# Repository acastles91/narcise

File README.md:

# Installation instructions

1. Download [Visual Studio Code](https://code.visualstudio.com/) and once that is done, install [PlatformIO](https://docs.platformio.org/en/latest/integration/ide/vscode.html#installation).
2. Open a terminal window and install *numpy*, a python library, by running the following command in the terminal:
`pip3 install numpy`
3. Clone this repository in a folder that you can remember, by typing the following command into the terminal:
`git clone https://github.com/acastles91/narcise/`
	* Navigate through folders using the command `cd`
4. In **Visual Studio Code** go to *File > Open Folder* and open the folder *narciseFromScratch* inside the *narcise* directory that you just cloned. This is where you will compile the code that will go into the microcontroller.
5. Navigate to the *narcise* folder with the file browser. Inside of it you will find a directory called *scriptGenerator*. Open the file *script* with **TextEdit**.
6. Edit the script. Each line represents a keyframe, which you define by first defining the *Timestamp* with the format *hh:mm:ss:fff*, where fff represents fractions of a second in milliseconds. After that comes the value of opacity of each layer as a percentage, with 100 being transparent and 0 being totally opaque. It is important that you keep this format consistent throughout the whole file. Make sure that you leave **no extra whitespace at the end of the file*
7. After saving the script, go back to *Visual Studio Code*, with the folder *narciseFromScratch* opened. Go to the terminal and type:
`cd ../scriptGenerator`
`python3 scriptGenerator.py 1 200 7`

	The argument `1` means that the script will be looped, `200` is the refresh rate (the bigger the value the slower and more "flickery" the piece will look) and `7` is a parameter that relates to the difference between minimal and maximal value. Play around with this last parameter to see differences in the response time of the dimming.

8. After the script is generated, connect the microcontroller to the computer using a USB cable capable of transfering data and upload the program.

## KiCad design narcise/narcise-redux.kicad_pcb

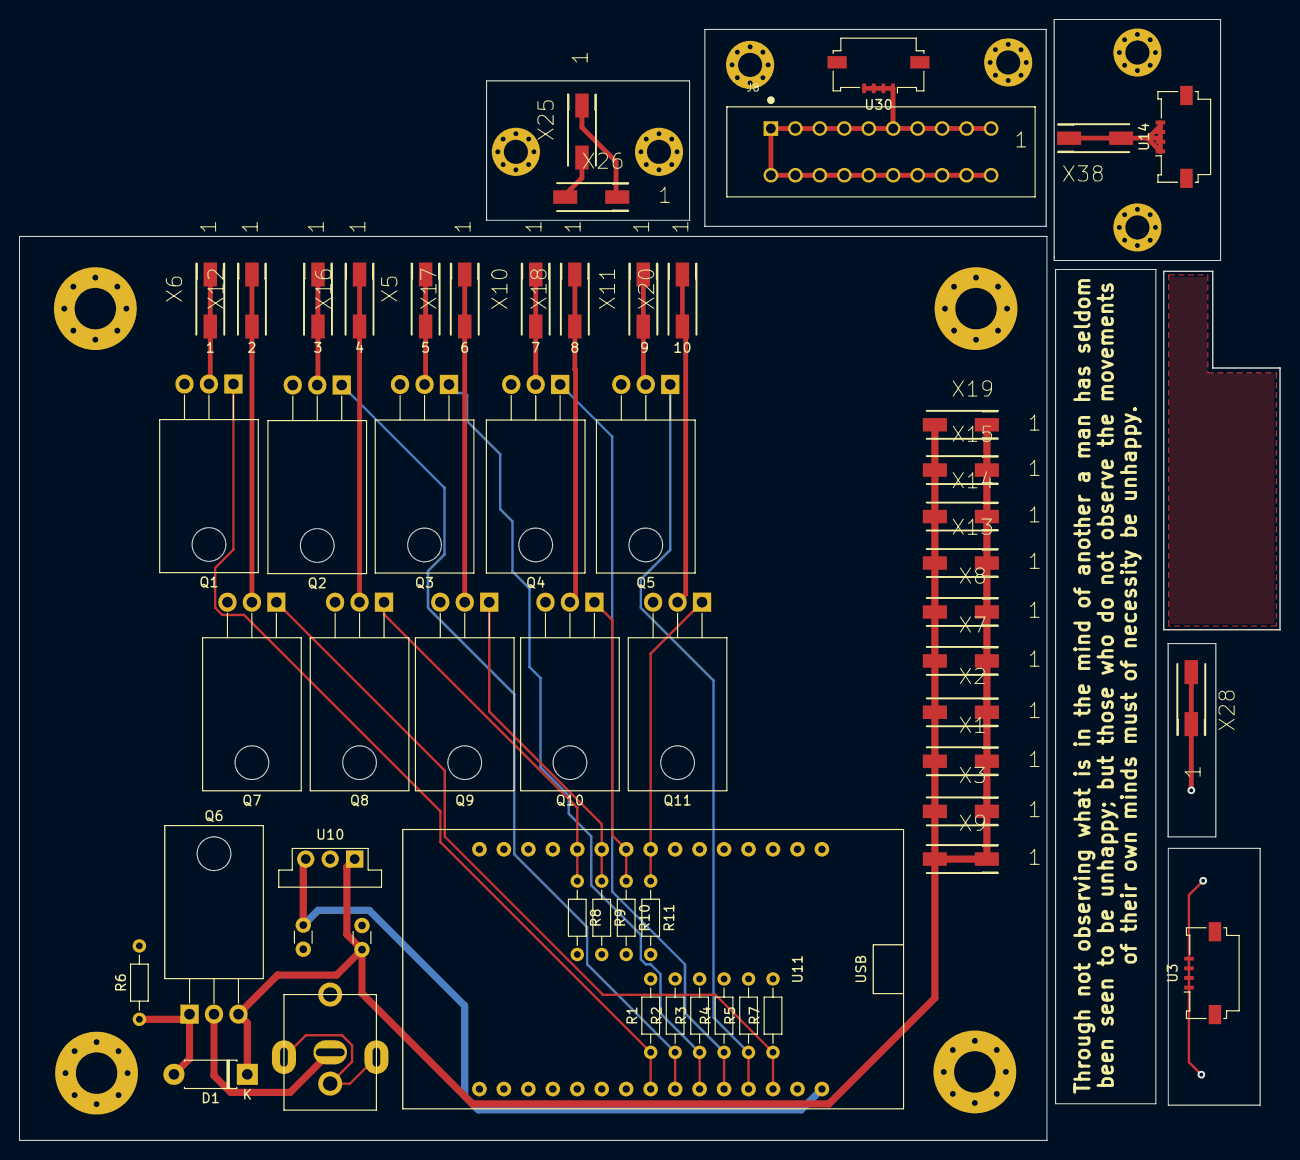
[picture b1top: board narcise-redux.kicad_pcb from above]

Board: 2 copper layers, 130.9 x 116.4 mm, 56 parts (0 on the bottom side), 31 nets.

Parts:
D1: D_Zener-10V; D_DO-41_SOD81_P7.62mm_Horizontal
J8: 5-5530843-0; TE_5-5530843-0
Murata-Ceramic-Capacitor-50v1-22uF1, Murata-Ceramic-Capacitor-50v1-22uF2: C; C_Disc_D3.0mm_W1.6mm_P2.50mm
Q1, Q2, Q3, Q4, Q5, Q7, Q8, Q9, Q10, Q11: IRLZ44N-horizontal; TO-220-3_Horizontal_TabDown
Q6: IRF5305-Reverse-Polarity; TO-220-3_Horizontal_TabDown
R1, R2, R3, R4, R5, R7, R8, R9, R10, R11: R; R_Axial_DIN0204_L3.6mm_D1.6mm_P7.62mm_Horizontal
R6: 100K; R_Axial_DIN0204_L3.6mm_D1.6mm_P7.62mm_Horizontal
U3, U14: fpc-connector-mosfet-drain; Molex_200528-0040_1x04-1MP_P1.00mm_Horizontal
U10: OKI-78SR-5v; Converter_DCDC_muRata_OKI-78SR_Vertical
U11: ariadne-rescue_ESP32-WROOM-32D-ariadne; ESP32-DEVKIT
U21: POWER_CONNECTOR-DCJ250-20-B-K1-A; POWER_JACK_DCJ250-20-B-K1-A
U30: fpc-connector-VIN; Molex_200528-0040_1x04-1MP_P1.00mm_Horizontal
X1, X2, X3, X4, X5, X6, X7, X8, X9, X10, X11, X12, X13, X14, X15, X16, X17, X18, X19, X20, X25, X26, X28, X38: 2059-301_998-403; 998-403

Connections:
+5V: Murata-Ceramic-Capacitor-50v1-22uF2.1, U10.3, U11.15
+24V: D1.1, Murata-Ceramic-Capacitor-50v1-22uF1.1, Q6.3, U10.1, X1.L1.1, X1.L1.2, X2.L1.1, X2.L1.2, X3.L1.1, X3.L1.2, X7.L1.1, X7.L1.2, X8.L1.1, X8.L1.2, X9.L1.1, X9.L1.2, X13.L1.1, X13.L1.2, X14.L1.1, X14.L1.2, X15.L1.1, X15.L1.2, X19.L1.1, X19.L1.2
unnamed: D1.2, Q6.1, R6.1
unnamed: J8.1, J8.2, J8.3, J8.4, J8.5, J8.6, J8.7, J8.8, J8.9, J8.10, J8.11, J8.12, J8.13, J8.14, J8.15, J8.16, J8.17, J8.18, J8.19, J8.20, U30.1, U30.2, U30.3, U30.4
unnamed: Q1.2, X6.L1.1, X6.L1.2
unnamed: Q2.2, X4.L1.1, X4.L1.2
unnamed: Q3.2, X5.L1.1, X5.L1.2
unnamed: Q4.2, X10.L1.1, X10.L1.2
unnamed: Q5.2, X11.L1.1, X11.L1.2
unnamed: Q7.2, X12.L1.1, X12.L1.2
unnamed: Q8.2, X16.L1.1, X16.L1.2
unnamed: Q9.2, X17.L1.1, X17.L1.2
unnamed: Q10.2, X18.L1.1, X18.L1.2
unnamed: Q11.2, X20.L1.1, X20.L1.2
unnamed: U3.1, U3.2, U3.3, U3.4
unnamed: U14.1, U14.2, U14.3, U14.4, X38.L1.1, X38.L1.2
unnamed: X25.L1.1, X26.L1.1
unnamed: X25.L1.2, X26.L1.2
unnamed: X28.L1.1, X28.L1.2
POWER-IN+: Q6.2, U21.1
POWER-IN-: Murata-Ceramic-Capacitor-50v1-22uF1.2, Murata-Ceramic-Capacitor-50v1-22uF2.2, Q1.3, Q2.3, Q3.3, Q4.3, Q5.3, Q7.3, Q8.3, Q9.3, Q10.3, Q11.3, R1.2, R2.2, R3.2, R4.2, R5.2, R6.2, R7.2, R8.2, R9.2, R10.2, R11.2, U10.2, U11.14, U11.17, U21.2
sheet1: Q1.1, R1.1, U11.8
sheet2: Q2.1, R2.1, U11.9
sheet3: Q3.1, R3.1, U11.10
sheet4: Q4.1, R4.1, U11.11
sheet5: Q5.1, R5.1, U11.12
sheet6: Q7.1, R7.1, U11.13
sheet7: Q8.1, R8.1, U11.26
sheet8: Q9.1, R9.1, U11.25
sheet9: Q10.1, R10.1, U11.24
sheet10: Q11.1, R11.1, U11.23

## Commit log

2021-02-15 New dimmer libraries https://github.com/RobotDynOfficial/RBDDimmer
2021-03-05 Before moving to Desktop
2021-03-17 After PCB order
2021-04-01 After DHL delivery
2021-04-01 correction
2021-04-01 updated gitignore
2021-04-11 esto es una prueba
2021-05-05 troubleshooting
2021-05-09 Trouble
2021-05-09 geting there
2021-05-09 por favor
2021-05-09 changed ledcWrite for analogWrite
2021-05-09 something??
2021-05-11 Three ticks
